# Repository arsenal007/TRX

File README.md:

DIY HF Transceiver
	1) KiCAD PCBs:
		1.1 VFOs
		1.2 MAINBOARDs
		1.3 BPFs
		1.4 AMPs
	2)  VFO firmware
	3) measurements

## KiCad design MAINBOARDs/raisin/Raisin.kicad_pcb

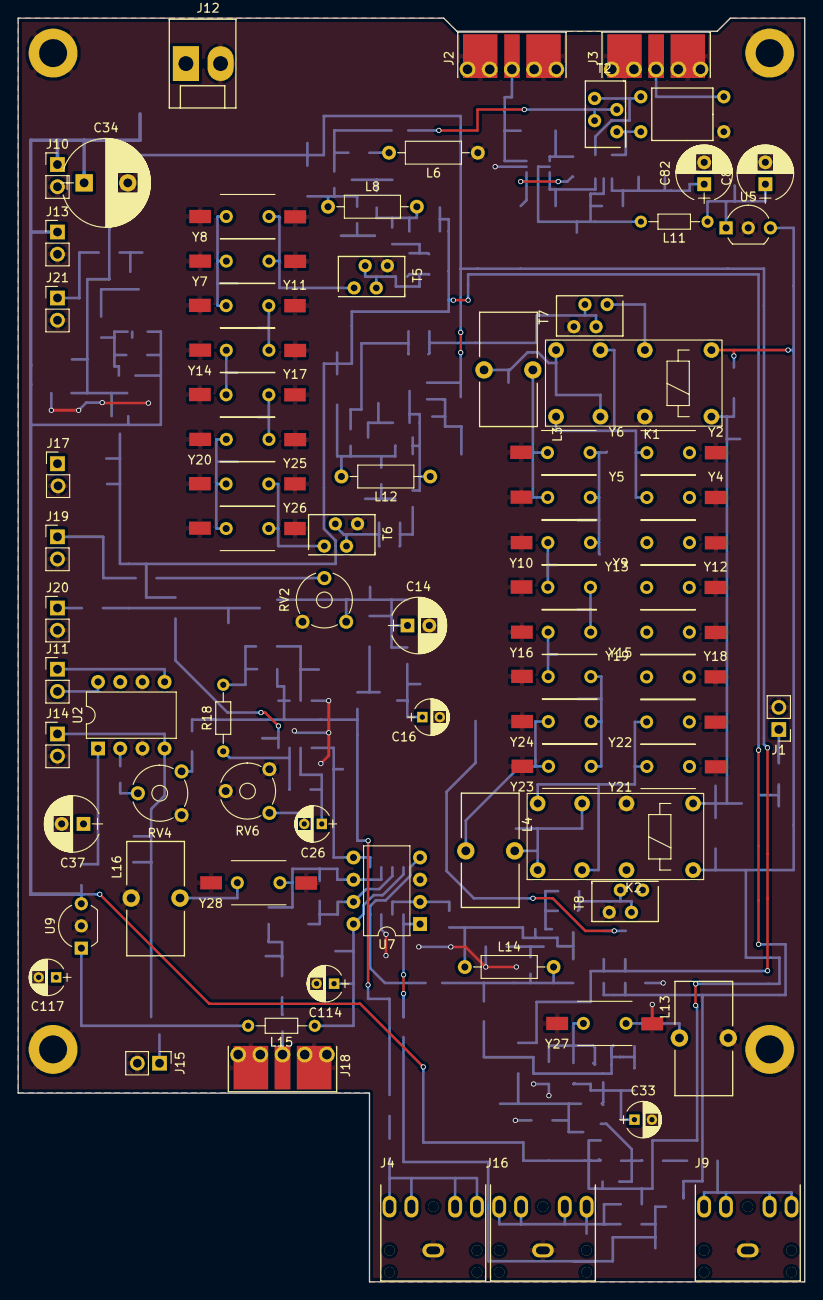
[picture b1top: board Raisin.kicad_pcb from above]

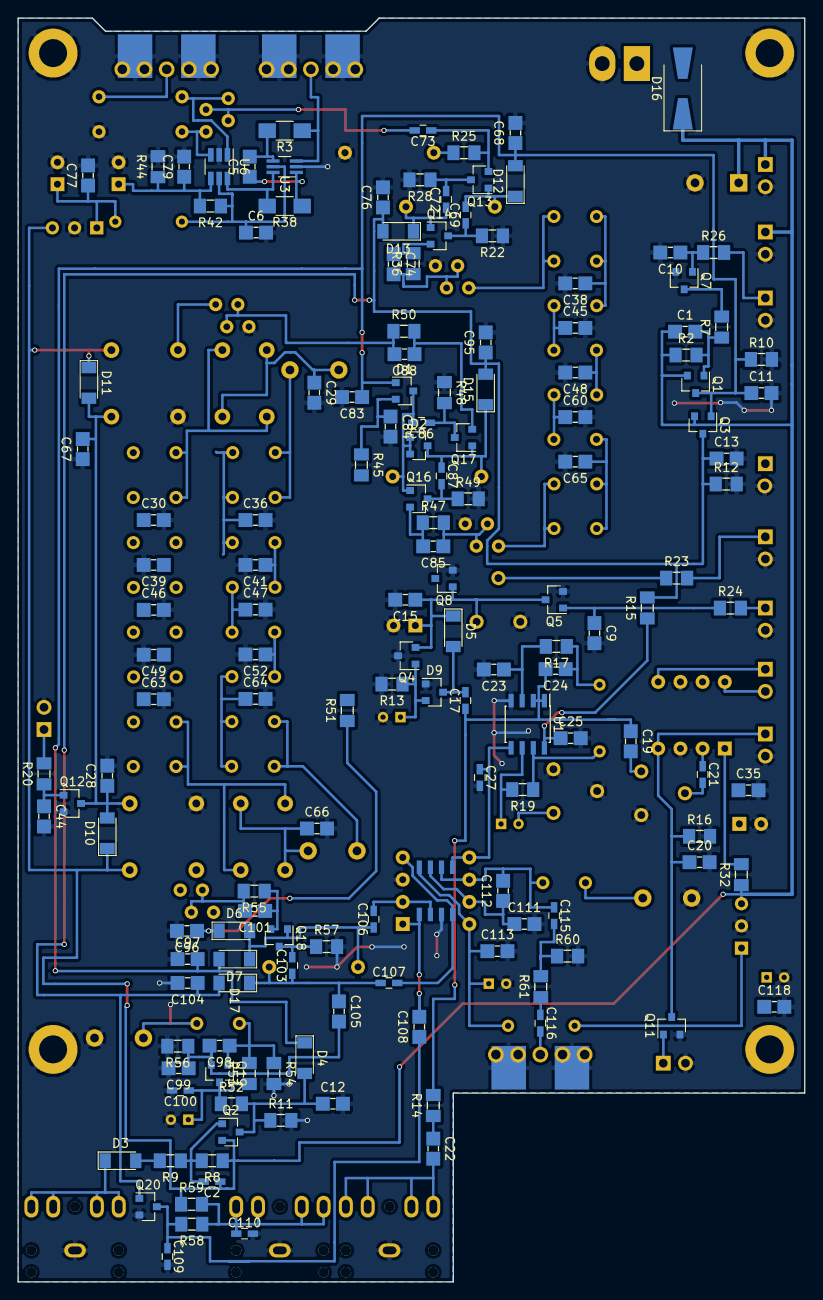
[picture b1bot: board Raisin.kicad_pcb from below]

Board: 2 copper layers, 90.0 x 144.6 mm, 234 parts (151 on the bottom side), 117 nets.

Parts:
C1, C5, C6, C9, C10, C11, C12, C13, C15, C25, C28, C35, C44, C67, C68, C74, C76, C77, C79, C83, C84, C85, C88, C95, C96, C97, C101, C104, C108, C113, C118: 100nF; C_1206_0603
C2, C17, C21, C100: 100nF; C_0603_HandSoldering
C14: 33uF; CP_Radial_D6.3mm_P2.50mm
C16: 1uF; CP_Radial_D4.0mm_P2.00mm
C19, C20, C22: 1uF; C_1206_0603
C23: 4n7; C_1206_0603
C24: 47n; C_1206_0603
C26, C33, C114, C117: 10uF; CP_Radial_D4.0mm_P2.00mm
C27, C69, C72, C73, C86, C87, C103, C106, C107, C109, C110, C115, C116: 10nF; C_0603_HandSoldering
C29, C30, C36, C38, C39, C41, C45, C46, C47, C48, C49, C52, C60, C63, C64, C65, C66: 100pF*; C_1206_0603
C34: 330uF; CP_Radial_D10.0mm_P5.00mm
C37: 220uF; CP_Radial_D6.3mm_P2.50mm
C80, C82: 22uF; CP_Radial_D6.3mm_P2.50mm
C98: 100pF; C_1206_0603
C99: 180pF; C_1206_0603
C105: 10pF*; C_1206_0603
C111: 22pF*/100nF; C_1206_0603
C112: 22pF; C_1206_0603
D1, D2, D9: BAV99; SOT-23
D3, D4, D5, D6, D7, D12, D13, D15, D17: LL4148; D_MiniMELF
D10, D11: D; D_MiniMELF
D16: SS14; D_SMA-SMB_Universal_Handsoldering
J1: CW; Pin_Header_Straight_1x02_Pitch2.54mm
J2, J3, J18: Conn_Coaxial; RFCONNECTOR
J4: Line OUT; audio_jack_3_5mm_PJ307
J5, J6, J7, J8: Conn_01x01; MountingHole_3.2mm_M3_DIN965_Pad
J9: Key; audio_jack_3_5mm_PJ307
J10: ATT; Pin_Header_Straight_1x02_Pitch2.54mm
J11: Speaker; Pin_Header_Straight_1x02_Pitch2.54mm
J12: POWER; Molex_KK-41791-02_02x3.96mm_Straight
J13, J17: BPF; Pin_Header_Straight_1x02_Pitch2.54mm
J14: AMP; Pin_Header_Straight_1x02_Pitch2.54mm
J15: TX; Pin_Header_Straight_1x02_Pitch2.54mm
J16: MIC; audio_jack_3_5mm_PJ307
J19: S-metr; Pin_Header_Straight_1x02_Pitch2.54mm
J20: AGC_OFF; Pin_Header_Straight_1x02_Pitch2.54mm
J21: TX_SYNT; Pin_Header_Straight_1x02_Pitch2.54mm
K1, K2: RS-12
L3, L4: L; Choke_Toroid_6,5x13mm_Vertical
L6, L8, L12, L14: 22uH; R_Axial_DIN0207_L6.3mm_D2.5mm_P10.16mm_Horizontal
L11, L15: 47uH; R_Axial_DIN0204_L3.6mm_D1.6mm_P7.62mm_Horizontal
L13, L16: L_Small; Choke_Toroid_6,5x13mm_Vertical
Q1, Q2, Q3: Si2301-TP; SOT-23
Q4: MMBT3906; SOT-23
Q5, Q7, Q8, Q11: 2N7002; SOT-23
Q12: MMBT2222; SOT-23
Q13, Q14, Q16, Q17, Q18: MMBFJ310LT1G; SOT-23
Q19: MMBT2222LT1G; SOT-23
Q20: BSS138; SOT-23
R2, R7, R8, R9: 2.7k; R_1206_0603
R3, R38: 1M; R_1206_HandSoldering
R10, R11, R12, R45: 4.7k; R_1206_0603
R13, R16: 150k*; R_1206_0603
R14, R15: 100; R_1206_0603
R17, R19, R59: 15k; R_1206_0603
R18: 1k; R_Axial_DIN0204_L3.6mm_D1.6mm_P7.62mm_Horizontal
R20: 2k; R_1206_0603
R22, R28: 220; R_1206_0603
R23: 12k; R_1206_0603
R24, R26: 2.2k; R_1206_0603
R25, R36, R47, R50, R55: 30; R_1206_0603
R32: 0*; R_1206_0603
R42, R44: 3,3k; R_1206_0603
R48, R49: 1.5k*; R_1206_0603
R51, R58, R60, R61: 1k; R_1206_0603
R52: 100R; R_1206_0603
R53: 100k; R_1206_0603
R54: 200k; R_1206_0603
R56: 750*; R_1206_0603
R57: 10k; R_1206_0603
RV2: 1M; Potentiometer_Trimmer_Piher_PT-6v_Horizontal
RV4: 33k; Potentiometer_Trimmer_Piher_PT-6v_Horizontal
RV6: 1k; Potentiometer_Trimmer_Piher_PT-6v_Horizontal
T1: 1:2; TF_2
T2, T5, T6, T7, T8: Transformer; TF14
U1: NE5532; SOIC-8_3.9x4.9mm_Pitch1.27mm
U2: TDA7052A; DIP-8_W7.62mm
U3: NC7WZ04; SOT-363_SC-70-6_Handsoldering
U5: L78L05_TO92; TO-92_Inline_Wide
U6: FSA3157L6X; SOT-23-6_Handsoldering
U7: SA612A; DIP-8_SOIC-8_W7.62mm
U9: L78L06_TO92; TO-92_Inline_Wide
Y2, Y4, Y10, Y12, Y16, Y18, Y23, Y24: Crystal_GND23_Small; Crystal_HC49-U_Vertical_3GND
Y5, Y6, Y9, Y13, Y15, Y19, Y21, Y22: Crystal_GND23_Small; Crystal_HC49-U_Vertical_4GND
Y7, Y8, Y11, Y14, Y17, Y20, Y25, Y26, Y27, Y28: Crystal_GND23_Small; Crystal_HC49-U_Vertical

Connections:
+12V: C1.1, C2.1, C34.1, D10.1, D11.1, D16.1, J10.1, J13.1, J17.1, K1.9, K2.8, Q1.2, Q2.2, Q3.2, R2.1, R8.1, R32.1, R59.1, U5.3, U9.3
AGC: Q8.3, R45.2, R51.2
AGC_OFF: J20.1, R24.2
AUDIO: C27.1, U1.5, U7.5
BFO: C116.2, J18.1
BPF: J3.1, T1.1
CW: J1.1, R20.2
CW_TONE: C12.1, D4.2, Q2.3, R11.1, R52.2
GND: C6.2, C9.2, C10.2, C11.2, C12.2, C13.2, C14.2, C15.2, C16.2, C20.2, C23.2, C25.2, C27.2, C28.2, C29.2, C30.2, C33.2, C34.2, C35.2, C36.2, C37.2, C38.2, C39.2, C41.2, C44.2, C45.2, C46.2, C47.2, C48.2, C49.2, C52.2, C60.2, C63.2, C64.2, C65.2, C66.2, C67.1, C68.2, C76.2, C77.2, C79.2, C80.2, C82.2, C83.2, C84.2, C95.2, C96.2, C97.1, C99.2, C100.2, C104.2, C109.2, C110.2, C111.2, C113.2, C114.2, C117.2, C118.2, D9.1, J1.2, J2.2, J3.2, J4.3, J5.1, J6.1, J7.1, J8.1, J9.3, J10.2, J12.2, J13.2, J14.2, J15.2, J16.3, J17.2, J18.2, J19.2, J20.2, J21.2, K1.5, K2.12, L6.1, L13.1, L16.2, Q4.3, Q5.2, Q7.2, Q8.2, Q11.2, Q12.2, Q20.2, R10.2, R11.2, R12.2, R13.2, R16.2, R22.1, R28.2, R44.2, R48.1, R49.2, R54.2, R56.2, R57.2, R60.2, RV2.3, RV4.3, RV6.1, RV6.2, T1.2, T5.4, T6.4, T7.4, T8.4, U1.4, U2.3, U2.6, U3.2, U5.2, U6.2, U7.3, U9.2, Y2.3, Y4.3, Y5.4, Y6.4, Y7.3, Y7.4, Y8.3, Y8.4, Y9.4, Y10.3, Y11.3, Y11.4, Y12.3, Y13.4, Y14.3, Y14.4, Y15.4, Y16.3, Y17.3, Y17.4, Y18.3, Y19.4, Y20.3, Y20.4, Y21.4, Y22.4, Y23.3, Y24.3, Y25.3, Y25.4, Y26.3, Y26.4, Y27.3, Y27.4, Y28.3, Y28.4
unnamed: C1.2, Q1.1, R2.2, R7.1
unnamed: C2.2, Q2.1, R8.2, R9.1
unnamed: C5.1, R38.1, U3.1
unnamed: C5.2, R3.2, U3.4
unnamed: C9.1, Q5.1, R24.1
unnamed: C10.1, Q7.1, R26.1
unnamed: C14.1, C15.1, D5.1, Q4.2, Q5.3, Q8.1, RV2.1
unnamed: C16.1, D9.2, Q4.1, R13.1
unnamed: C17.1, C19.1, C24.2, R14.2, U1.1, U1.2
unnamed: C17.2, D5.2, D9.3
unnamed: C19.2, RV4.1
unnamed: C20.1, J14.1, Q11.3, R16.1, U2.4
unnamed: C21.1, U2.2
unnamed: C21.2, RV4.2
unnamed: C22.1, R14.1
unnamed: C22.2, J4.1, J4.2, J4.4, J4.5
unnamed: C23.1, R17.2, U1.3
unnamed: C24.1, R17.1, R18.2
unnamed: C25.1, R15.1, U1.8
unnamed: C26.1, R19.2, U1.6
unnamed: C26.2, RV6.3
unnamed: C28.1, C67.2, D10.2, D11.2, K1.8, K2.9, Q12.3
unnamed: C29.1, K1.3, K1.16, L3.1
unnamed: C30.1, Y2.2, Y4.2, Y9.1
unnamed: C35.1, C37.1, R32.2, U2.1
unnamed: C36.1, Y5.2, Y6.2, Y10.1
unnamed: C38.1, Y7.2, Y8.2, Y11.1
unnamed: C39.1, Y9.2, Y12.1
unnamed: C41.1, Y10.2, Y13.1
unnamed: C44.1, Q12.1, R20.1
unnamed: C45.1, Y11.2, Y14.1
unnamed: C46.1, Y12.2, Y15.1
unnamed: C47.1, Y13.2, Y16.1
unnamed: C48.1, Y14.2, Y17.1
unnamed: C49.1, Y15.2, Y18.1
unnamed: C52.1, Y16.2, Y19.1
unnamed: C60.1, Y17.2, Y20.1
unnamed: C63.1, Y18.2, Y21.1, Y22.1
unnamed: C64.1, Y19.2, Y23.1, Y24.1
unnamed: C65.1, Y20.2, Y25.1, Y26.1
unnamed: C66.1, K2.1, K2.14, L4.2
unnamed: C69.1, Q14.3, R22.2
unnamed: C69.2, D12.1, L8.1, Q13.1
unnamed: C72.1, D13.1, L8.2, Q14.1
unnamed: C72.2, Q13.3, R28.1
unnamed: C73.1, Q13.2, R25.2
unnamed: C73.2, T2.2, T2.3
unnamed: C74.1, Q14.2, R36.2
unnamed: C74.2, R36.1, T5.2, T5.3
unnamed: C77.1, C80.1, L11.1, U5.1
unnamed: C79.1, C82.1, R42.2, R44.1, U6.4
unnamed: C84.1, D1.2, R45.1
unnamed: C85.1, R47.2, T6.2, T6.3
unnamed: C85.2, Q16.2, R47.1
unnamed: C86.1, Q17.3, R48.2
unnamed: C86.2, D1.3, D2.1, D2.2, L12.1, Q16.1
unnamed: C87.1, D2.3, D15.1, L12.2, Q17.1
unnamed: C87.2, Q16.3, R49.1
unnamed: C88.1, Q17.2, R50.2
unnamed: C88.2, R50.1, T7.2, T7.3
unnamed: C96.1, D6.1, R51.1
unnamed: C98.1, Q19.1, R53.2, R54.1, Y27.2
unnamed: C33.1, C100.1, Q19.3, R52.1, R53.1
unnamed: C101.1, Q18.2, R55.1
unnamed: C101.2, R55.2, T8.2, T8.3
unnamed: C103.1, C105.1, C107.1, D17.1, L14.2
unnamed: C103.2, Q18.3, R57.1
unnamed: C98.2, C99.1, C105.2, Q19.2, R56.1
unnamed: C106.1, D6.2, D7.1, L14.1, Q18.1
unnamed: C106.2, U7.2
unnamed: C107.2, U7.4
unnamed: C108.1, C109.1, Q20.3, R58.2
unnamed: C108.2, U7.1
unnamed: C110.1, J16.1, J16.2, J16.4, J16.5, R58.1, R59.2
unnamed: C111.1, C112.1, U7.7
unnamed: C112.2, C115.1, U7.6, Y28.1
unnamed: C113.1, C114.1, L15.1, U7.8
unnamed: C115.2, R60.1, R61.2
unnamed: C116.1, R61.1
unnamed: C117.1, C118.1, L15.2, U9.1
unnamed: D3.1, J9.1, J9.2, J9.4, J9.5
unnamed: D3.2, R9.2
unnamed: D16.2, J12.1
unnamed: J11.1, U2.5
unnamed: J11.2, U2.8
unnamed: J19.1, R23.2
unnamed: K1.1, K1.14, Y2.1, Y4.1
unnamed: K2.3, K2.16, Y21.2, Y22.2
unnamed: L3.2, Y5.1, Y6.1
unnamed: L4.1, Y23.2, Y24.2
unnamed: L6.2, R25.1
unnamed: L13.2, Y27.1
unnamed: L16.1, Y28.2
unnamed: Q7.3, R7.2
unnamed: R18.1, R19.1, U1.7
unnamed: R38.2, U3.6, U6.6
unnamed: T1.3, T2.4, U6.1
unnamed: T1.4, T2.1, U6.3
QER11: T5.1, Y7.1, Y8.1
QER12: T6.1, Y25.2, Y26.2
QER21: K1.12, T7.1
QER22: K2.5, T8.1
RX: C13.1, C76.1, C95.1, C104.1, D13.2, D15.2, D17.2, Q3.3, Q20.1, R12.1, R15.2
S-metr: R23.1, RV2.2
TX: C11.1, C68.1, C83.1, C97.2, D1.1, D4.1, D7.2, D12.2, J15.1, Q1.3, Q3.1, Q11.1, R10.1
TX_SYNT: J21.1, R26.2
VCC: C6.1, L11.2, R42.1, U3.5, U6.5
VFO: J2.1, R3.1, U3.3

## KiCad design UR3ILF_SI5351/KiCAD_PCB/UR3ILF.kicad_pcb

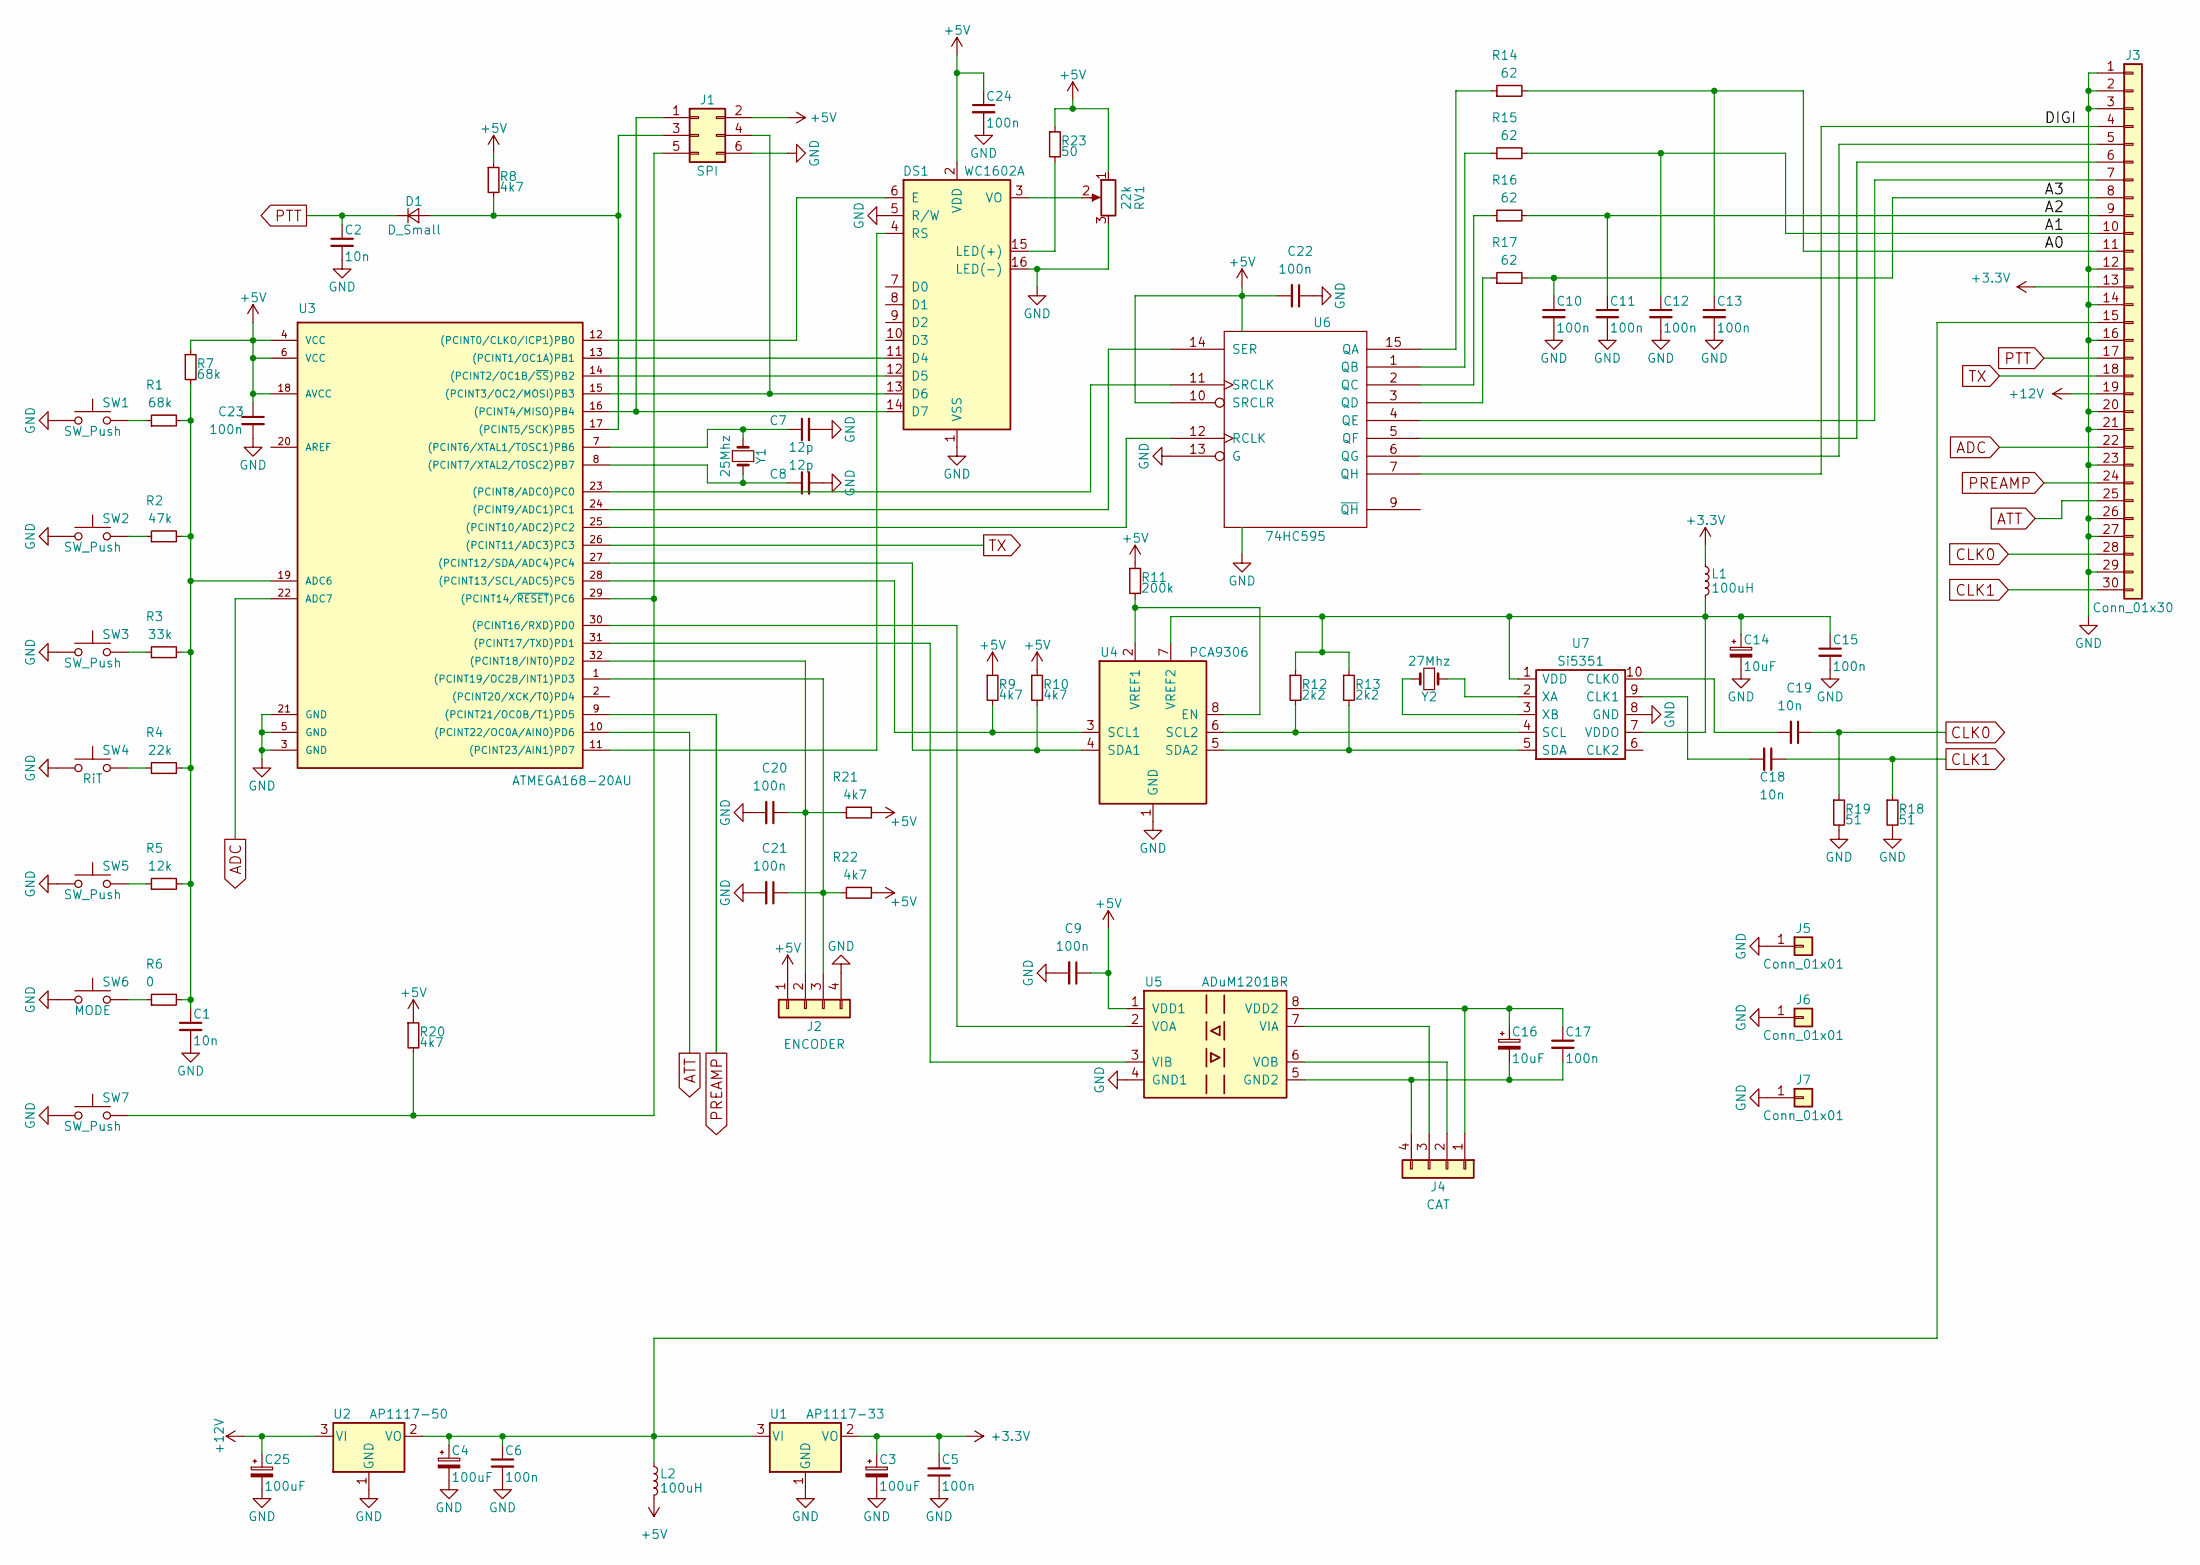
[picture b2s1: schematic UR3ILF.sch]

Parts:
C1, C2: 10n; C_Disc_D4.3mm_W1.9mm_P5.00mm
C3, C4, C25: 100uF; CP_Tantalum_Case-D_EIA-7343-31_Hand
C5, C6, C9, C10, C11, C12, C13, C15, C17, C20, C21, C22, C23, C24: 100n; C_1206_0603
C7, C8: 12p; C_Disc_D4.3mm_W1.9mm_P5.00mm
C14, C16: 10uF; CP_Tantalum_Case-A_EIA-3216-18_Wave
C18, C19: 10n; C_0603_HandSoldering
D1: D_Small; D_DO-35_SOD27_P10.16mm_Horizontal
DS1: WC1602A
J1: SPI; Pin_Header_Straight_2x03_Pitch2.54mm
J2: ENCODER; Pin_Header_Straight_1x04_Pitch2.54mm
J3: Conn_01x30; Pin_Header_Straight_1x30_Pitch2.54mm
J4: CAT; Pin_Header_Angled_1x04_Pitch2.54mm
J5, J6, J7: Conn_01x01; MountingHole_3.2mm_M3_DIN965_Pad
L1, L2: 100uH; R_Axial_DIN0204_L3.6mm_D1.6mm_P7.62mm_Horizontal
R1: 68k; R_1206_0603
R2: 47k; R_1206_0603
R3: 33k; R_1206_0603
R4: 22k; R_1206_0603
R5: 12k; R_1206_0603
R6: 0; R_1206_0603
R7: 68k; Resistor_SMD+THTuniversal_0603to2512_RM10_HandSoldering
R8, R20: 4k7; Resistor_SMD+THTuniversal_0603to2512_RM10_HandSoldering
R9, R10: 4k7; R_1206_0603
R11: 200k; R_1206_0603
R12, R13: 2k2; R_1206_0603
R14, R15, R16, R17: 62; R_1206_0603
R18, R19: 51; R_1206_0603
R21, R22: 4k7; R_Axial_DIN0207_L6.3mm_D2.5mm_P10.16mm_Horizontal
R23: 50; R_1206_0603
RV1: 22k; Potentiometer_Trimmer_Piher_PT-6v_Horizontal
SW1, SW2, SW3, SW5, SW7: SW_Push; SW_PUSH_6mm_h13mm
SW4: RiT; SW_PUSH_6mm_h13mm
SW6: MODE; SW_PUSH_6mm_h13mm
U1: AP1117-33; SOT-223
U2: AP1117-50; SOT-223
U3: ATMEGA168-20AU; TQFP-32_7x7mm_Pitch0.8mm
U4: PCA9306; SSOP-8_2.95x2.8mm_Pitch0.65mm
U5: ADuM1201BR; SOIC-8_3.9x4.9mm_Pitch1.27mm
U6: 74HC595; SOIC-16_3.9x9.9mm_Pitch1.27mm
U7: Si5351; MSOP-10_3x3mm_Pitch0.5mm
Y1: 25Mhz; Crystal_HC49-SD_SMD
Y2: 27Mhz; Crystal_HC49-SD_SMD

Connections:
+3V3: C3.1, C5.1, J3.13, L1.1, U1.2 (VO)
+5V: C9.1, C22.2, C23.1, C24.1, DS1.2 (VDD), J1.2, J2.1, L2.2, R7.1, R8.1, R9.1, R10.1, R11.1, R20.1, R21.2, R22.2, R23.1, RV1.1, U3.4 (VCC), U3.6 (VCC), U3.18 (AVCC), U5.1 (VDD1), U6.10 (SRCLR), U6.16 (VCC)
+12V: C25.1, J3.19, U2.3 (VI)
ADC: J3.22, U3.22 (ADC7)
ATT: J3.25, U3.10 ((PCINT22/OC0A/AIN0)PD6)
CLK0: C19.1, J3.28, R19.1
CLK1: C18.1, J3.30, R18.1
GND: C1.2, C2.2, C3.2, C4.2, C5.2, C6.2, C7.2, C8.2, C9.2, C10.2, C11.2, C12.2, C13.2, C14.2, C15.2, C20.2, C21.2, C22.1, C23.2, C24.2, C25.2, DS1.1 (VSS), DS1.5 (R/W), DS1.16 (LED(-)), J1.6, J2.4, J3.1, J3.2, J3.3, J3.12, J3.14, J3.16, J3.20, J3.21, J3.23, J3.26, J3.27, J3.29, J5.1, J6.1, J7.1, R18.2, R19.2, RV1.3, SW1.1, SW2.1, SW3.1, SW4.1, SW5.1, SW6.1, SW7.1, U1.1 (GND), U2.1 (GND), U3.3 (GND), U3.5 (GND), U3.21 (GND), U4.1 (GND), U5.4 (GND1), U6.8 (GND), U6.13 (G), U7.8 (GND)
unnamed: C1.1, R1.2, R2.2, R3.2, R4.2, R5.2, R6.2, R7.2, U3.19 (ADC6)
unnamed: C4.1, C6.1, J3.15, L2.1, U1.3 (VI), U2.2 (VO)
unnamed: C7.1, U3.7 ((PCINT6/XTAL1/TOSC1)PB6), Y1.1
unnamed: C8.1, U3.8 ((PCINT7/XTAL2/TOSC2)PB7), Y1.2
unnamed: C10.1, J3.8, R17.2
unnamed: C11.1, J3.9, R16.2
unnamed: C12.1, J3.10, R15.2
unnamed: C13.1, J3.11, R14.2
unnamed: C14.1, C15.1, L1.2, R12.1, R13.1, U4.7 (VREF2), U7.1 (VDD), U7.7 (VDDO)
unnamed: C16.1, C17.1, J4.1, U5.8 (VDD2)
unnamed: C16.2, C17.2, J4.4, U5.5 (GND2)
unnamed: C18.2, U7.9 (CLK1)
unnamed: C19.2, U7.10 (CLK0)
unnamed: C20.1, J2.2, R21.1, U3.32 ((PCINT18/INT0)PD2)
unnamed: C21.1, J2.3, R22.1, U3.1 ((PCINT19/OC2B/INT1)PD3)
unnamed: D1.2 (A), J1.3, R8.2, U3.17 ((PCINT5/SCK)PB5)
unnamed: DS1.3 (VO), RV1.2
unnamed: DS1.4 (RS), U3.11 ((PCINT23/AIN1)PD7)
unnamed: DS1.6 (E), U3.12 ((PCINT0/CLKO/ICP1)PB0)
unnamed: DS1.11 (D4), U3.13 ((PCINT1/OC1A)PB1)
unnamed: DS1.12 (D5), U3.14 ((PCINT2/OC1B/~SS~)PB2)
unnamed: DS1.13 (D6), J1.4, U3.15 ((PCINT3/OC2/MOSI)PB3)
unnamed: DS1.14 (D7), J1.1, U3.16 ((PCINT4/MISO)PB4)
unnamed: DS1.15 (LED(+)), R23.2
unnamed: J1.5, R20.2, SW7.2, U3.29 ((PCINT14/~RESET~)PC6)
unnamed: J3.4, U6.7 (QH)
unnamed: J3.5, U6.6 (QG)
unnamed: J3.6, U6.5 (QF)
unnamed: J3.7, U6.4 (QE)
unnamed: J4.2, U5.6 (VOB)
unnamed: J4.3, U5.7 (VIA)
unnamed: R1.1, SW1.2
unnamed: R2.1, SW2.2
unnamed: R3.1, SW3.2
unnamed: R4.1, SW4.2
unnamed: R5.1, SW5.2
unnamed: R6.1, SW6.2
unnamed: R9.2, U3.28 ((PCINT13/SCL/ADC5)PC5), U4.3 (SCL1)
unnamed: R10.2, U3.27 ((PCINT12/SDA/ADC4)PC4), U4.4 (SDA1)
unnamed: R11.2, U4.2 (VREF1), U4.8 (EN)
unnamed: R12.2, U4.6 (SCL2), U7.4 (SCL)
unnamed: R13.2, U4.5 (SDA2), U7.5 (SDA)
unnamed: R14.1, U6.15 (QA)
unnamed: R15.1, U6.1 (QB)
unnamed: R16.1, U6.2 (QC)
unnamed: R17.1, U6.3 (QD)
unnamed: U3.23 ((PCINT8/ADC0)PC0), U6.11 (SRCLK)
unnamed: U3.24 ((PCINT9/ADC1)PC1), U6.14 (SER)
unnamed: U3.25 ((PCINT10/ADC2)PC2), U6.12 (RCLK)
unnamed: U3.30 ((PCINT16/RXD)PD0), U5.2 (VOA)
unnamed: U3.31 ((PCINT17/TXD)PD1), U5.3 (VIB)
unnamed: U7.2 (XA), Y2.1
unnamed: U7.3 (XB), Y2.2
PREAMP: J3.24, U3.9 ((PCINT21/OC0B/T1)PD5)
PTT: C2.1, D1.1 (K), J3.17
TX: J3.18, U3.26 ((PCINT11/ADC3)PC3)

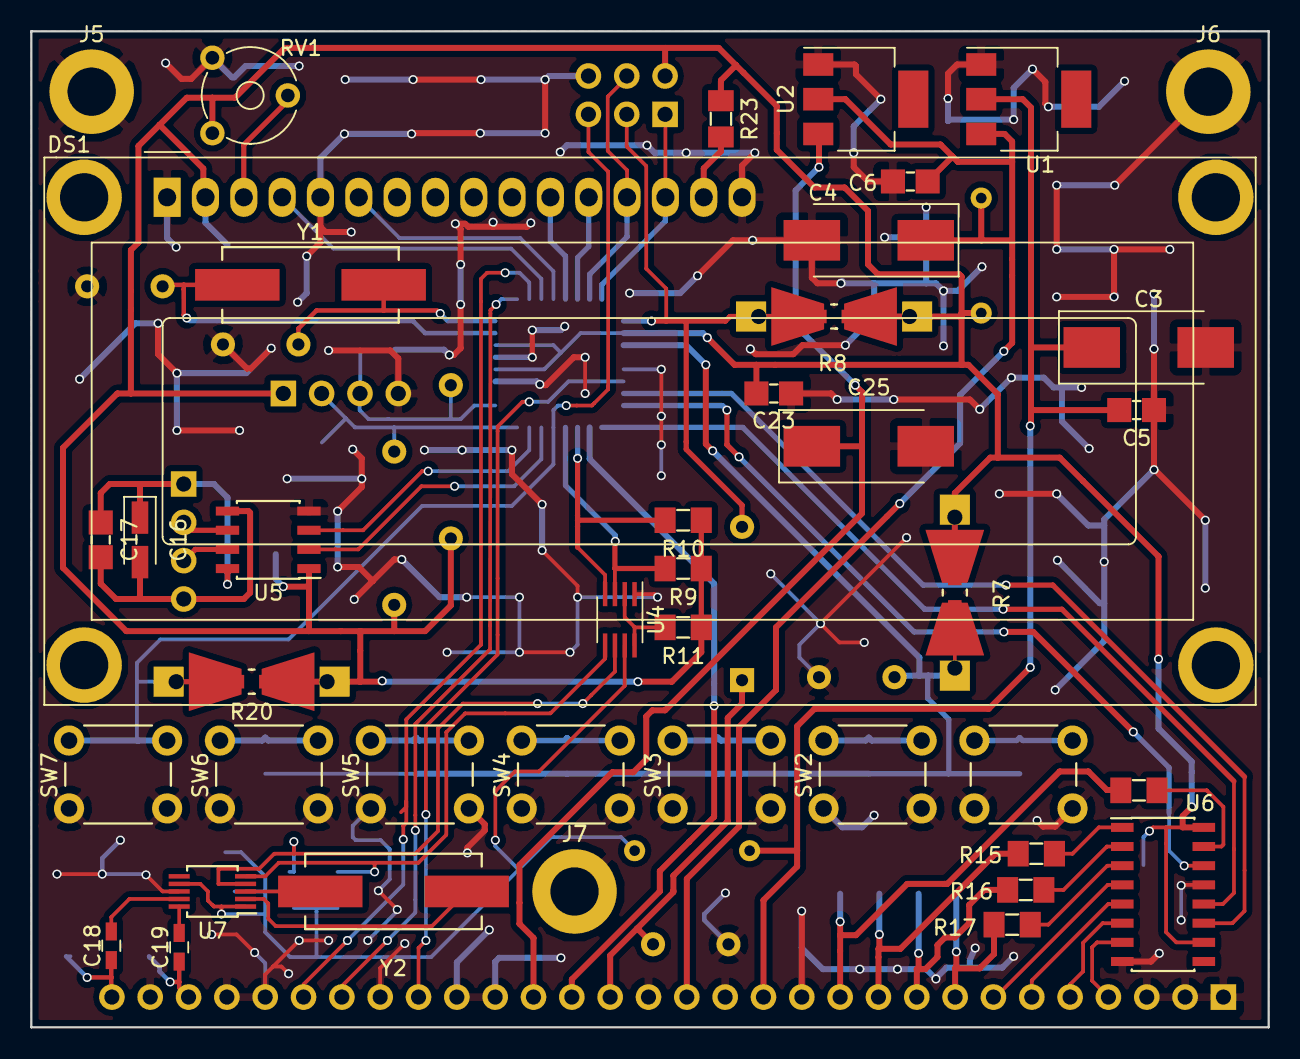
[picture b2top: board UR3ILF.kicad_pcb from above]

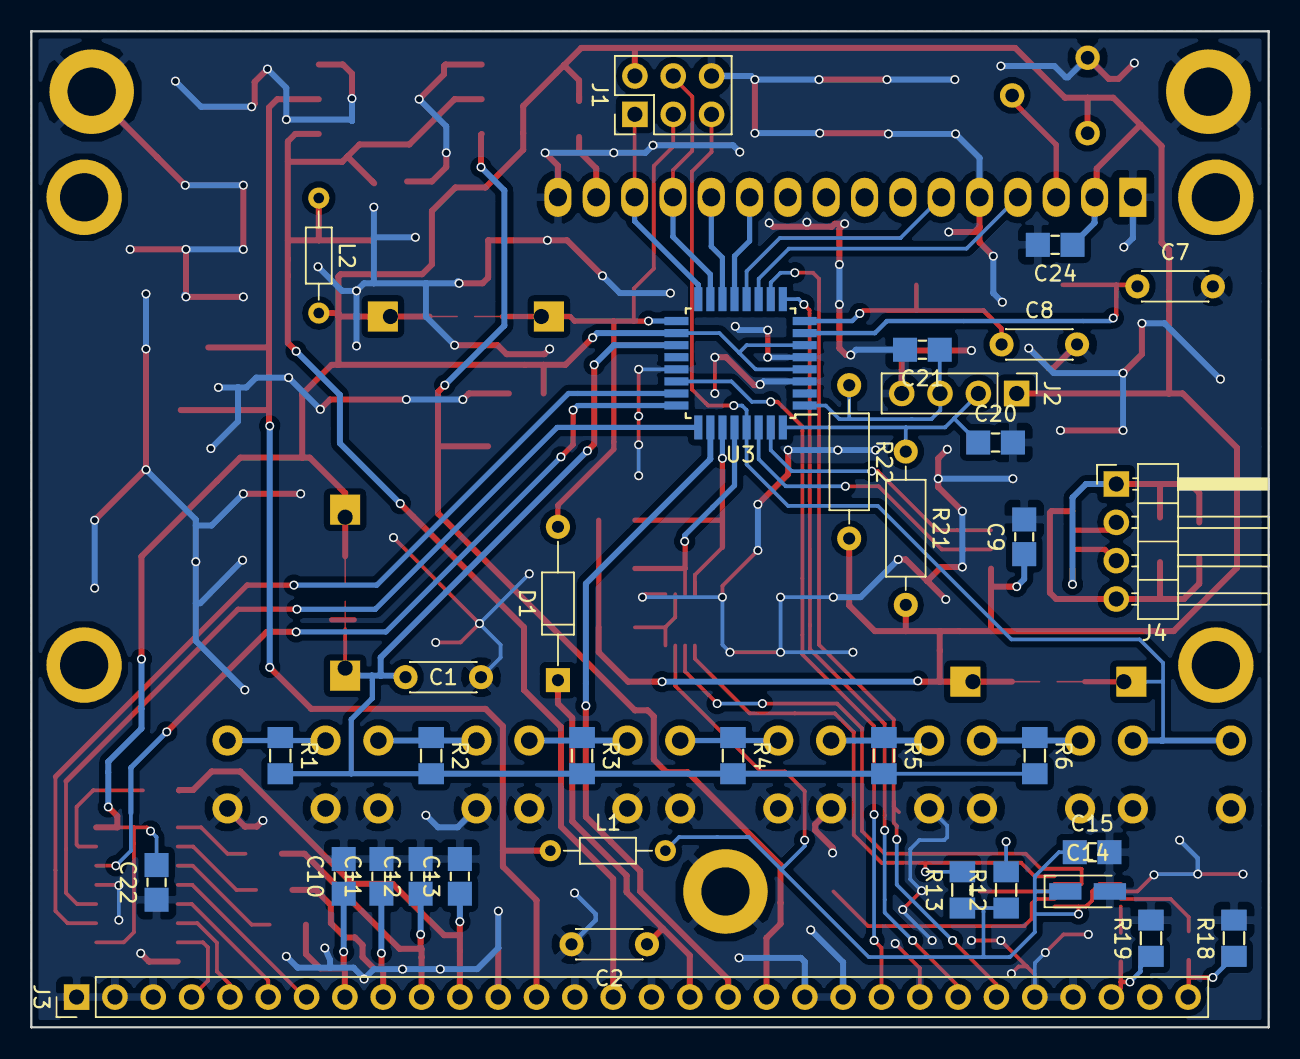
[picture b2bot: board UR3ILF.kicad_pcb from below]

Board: 2 copper layers, 82.0 x 66.0 mm, 76 parts (35 on the bottom side), 64 nets.

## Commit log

2019-06-15 bad pcb layout
2019-07-21 PCB to 0603, Buzzer
2019-08-13 Add GND connection points
2019-09-23 add VFO, UR3ILF, Si5351a
2019-09-23 move MAINBOARDs, ordering
2019-11-06 PCB almost ready
2019-11-10 DX PCB
